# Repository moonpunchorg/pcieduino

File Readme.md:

PCIeDuino
=========

Arduino on a mini-PCIe express card.

Based design from Arduino and [SparkFun's Pro Micro 3.3V][promicro] board.

License
=======

To follow the licensing of the original Arduino modules,
all of this is shared under [CC BY-SA 3.0][cc] 2014 Moonpunch.org

[promicro]: https://www.sparkfun.com/products/12587 "Pro Micro - 3.3V/8MHz"
[cc]: https://creativecommons.org/licenses/by-sa/3.0/ "Creative Commons Attribution Share-Alike"

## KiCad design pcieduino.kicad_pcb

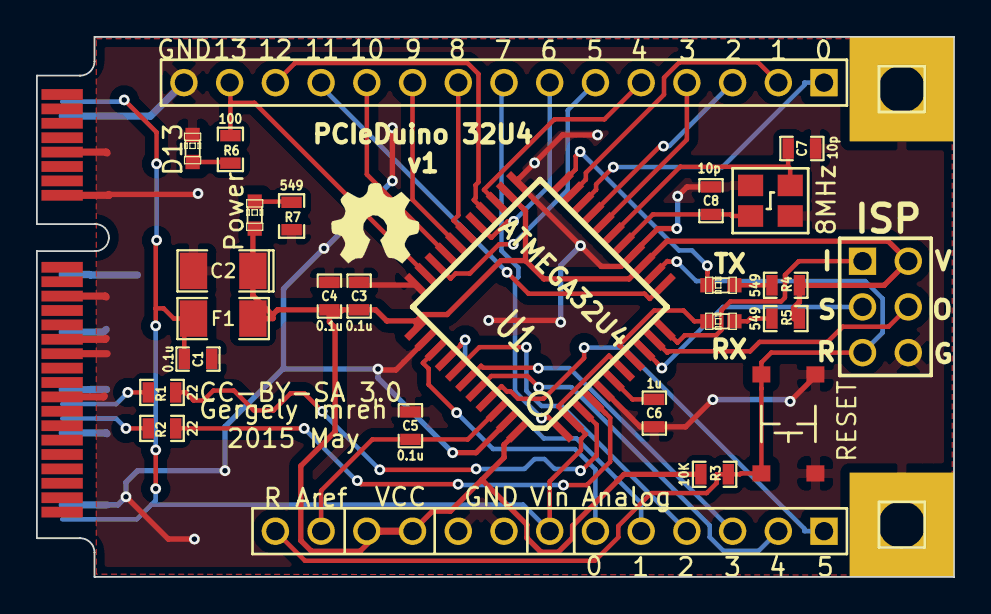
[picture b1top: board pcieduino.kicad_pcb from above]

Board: 2 copper layers, 51.0 x 30.0 mm, 29 parts (0 on the bottom side), 41 nets.

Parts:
C1, C3, C4, C5: 0.1u; SM0603_Capa
C2: 10u; SM1206POL
C6: 1u; SM0603_Capa
C7, C8: 10p; SM0603_Capa
D1: TX; LED-0603
D2: RX; LED-0603
D3: D13; LED-0603
D4: Power; LED-0603
F1: FUSE; SM1206
J1: PCIE-MINI; miniPCIeConn
J2: ISP; pin_array_3x2
J3: DIGITAL; PIN_ARRAY_15x1
J4: ANALOG_POWER; PIN_ARRAY_13x1
MOUNTING_HOLE1, MOUNTING_HOLE2: CONN_1; PIN_ARRAY_1
R1, R2: 22; SM0603_Resistor
R3: 10K; SM0603_Resistor
R4, R5, R7: 549; SM0603_Resistor
R6: 100; SM0603_Resistor
SW1: RESET; SMD_SWITCH
U1: ATMEGA32U4; TQFP44
X1: 8MHz; SMDXTAL_32x25

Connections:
/A0: J4.6, U1.36
/A1: J4.5, U1.37
/A2: J4.4, U1.38
/A3: J4.3, U1.39
/A4: J4.2, U1.40
/A5: J4.1, U1.41
/AREF: C5.1, J4.12, U1.42
/D0/RXI: J3.1, U1.20
/D1/TXO: J3.2, U1.21
/D2/SDA: J3.3, U1.19
/D3/SCL: J3.4, U1.18
/D4: J3.5, U1.25
/D5: J3.6, U1.31
/D6: J3.7, U1.27
/D7: J3.8, U1.1
/D8: J3.9, U1.28
/D9: J3.10, U1.29
/D10: J3.11, U1.30
/D11: J3.12, U1.12
/D12: J3.13, U1.26
/D13: J3.14, R6.1, U1.32
/D+: R2.1, U1.4
/D-: R1.1, U1.3
/MISO: J2.1, U1.11
/MOSI: J2.4, U1.10
/RESET: J2.5, J4.13, R3.2, SW1.2, U1.13
/RXLED: D2.2, U1.8
/SCK: J2.3, U1.9
/TXLED: D1.2, U1.22
/UVCC: C1.1, F1.1, J1.2, J1.52, J4.7, U1.2, U1.7
GND: C1.2, C2.2, C3.2, C4.2, C5.2, C6.2, C7.2, C8.2, D3.2, J1.4, J1.9, J1.15, J1.18, J1.21, J1.26, J1.27, J1.29, J1.34, J1.35, J1.40, J1.50, J2.6, J3.15, J4.8, J4.9, MOUNTING_HOLE1.1, MOUNTING_HOLE2.1, R7.2, SW1.1, U1.5, U1.15, U1.23, U1.33, U1.35, U1.43, X1.3
unnamed: J1.36, R1.2
unnamed: J1.38, R2.2
unnamed: C6.1, U1.6
unnamed: D4.2, R7.1
unnamed: C8.1, U1.16, X1.2
unnamed: C7.1, U1.17, X1.1
unnamed: D3.1, R6.2
unnamed: D1.1, R4.1
unnamed: D2.1, R5.1
VCC: C2.1, C3.1, C4.1, D4.1, F1.2, J2.2, J4.10, J4.11, R3.1, R4.2, R5.2, U1.14, U1.24, U1.34, U1.44

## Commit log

2014-08-21 work in progress
2014-08-23 add recent more progress
2014-08-24 finished first draft of schematic
2014-08-28 update connections
2014-10-11 latest updates starting to work on the PCB
2014-12-27 add .gitignore
2014-12-28 work in progress (footprint libraries)
2015-01-01 add miniPCIe connector pins footprint to library
2015-01-01 pcb: work in progress
2015-01-01 add footprint assignments
2015-01-03 add progress on 01/03
    Quick summary:
    * new crystal footprint
    * new switch footprint
    * combining digital pins
    * adding mounting holes
    ... and some small positioning changes
2015-01-03 more progress on 01/03
2015-01-04 add 01/04 changes
    summary:
    * redrawn the board starting from x=100.00, y=100.00 to have fix positioning
    * combine analog and power headers
    * remove RESET from power header because it already exists elsewhere
    * redraw fill zones with duplication
2015-01-05 progres on 01/05: mostly crystal work
2015-01-05 lock some components
2015-05-01 ATmega32U4 version work in progress
2015-05-01 updates to the schematic (simplifications, labels, power LED
2015-05-02 work in progress: Mouser part numbers, new switch footprint, fixed footprint mixups
2015-05-03 work in progress, after autorouting and all connections
2015-05-04 PCIeDuino32U4v1 submitted for printing at Seeed
2015-05-04 add gerbers
2015-05-24 Updated version, ready to print
    * fixed XTAL footprint
    * changed 10u bypass footprint
    * general layout improvements
    * added Moonpunch logo
2015-07-25 add PDF export of schematics
2015-07-25 update netlist
